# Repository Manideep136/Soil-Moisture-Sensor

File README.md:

# Soil Moisture Sensor PCB Using KiCad

## 📌 Project Overview

This project is a **Soil Moisture Sensor PCB** designed using KiCad 9. It detects the moisture level in soil using two conductive probes and an electronic sensing circuit.

The circuit uses an LM358 operational amplifier, a 10 kΩ potentiometer, resistors, capacitors, and indicator LEDs to detect changes in soil conductivity. The PCB includes two long sensing prongs that can be inserted into the soil.

The main objective of this project is to understand soil moisture detection, analog sensing circuits, and PCB design.

## 🎯 Objectives

- Design a soil moisture sensing circuit.
- Understand how soil conductivity changes with moisture.
- Use the LM358 for signal conditioning or threshold detection.
- Adjust the detection threshold using a potentiometer.
- Indicate the sensor status using LEDs.
- Design the schematic in KiCad.
- Assign component footprints.
- Create and route the PCB.
- Perform ERC and DRC checks.
- Visualize the completed PCB using KiCad's 3D Viewer.

## ⚙️ Working Principle

The sensor works by detecting changes in the electrical conductivity of soil.

The two sensing prongs act as electrodes. When inserted into soil, the electrical resistance between the electrodes changes depending on the soil's moisture content.

- **Wet soil:** Generally provides a lower resistance between the probes because it contains more conductive moisture.
- **Dry soil:** Generally provides a higher resistance between the probes.

The sensing circuit detects this change and provides a corresponding electrical signal.

The LM358 processes the sensing signal. The 10 kΩ potentiometer can be used to adjust the detection threshold, depending on the circuit configuration. The LEDs indicate the detected condition according to the actual circuit connections.

**Note:** The exact LED behavior depends on the schematic. Confirm which LED indicates wet or dry soil before using the sensor.

## 🔌 Block Diagram

```text
       Soil Moisture
             |
             v
      Two Sensing Probes
             |
             v
      Sensing Circuit
             |
             v
        LM358 Circuit
             |
             v
       Indicator LEDs
```

## 🧩 Components Used

| Reference | Component | Value / Type |
|---|---|---|
| U1 | Operational amplifier | LM358 |
| RV1 | Potentiometer | 10 kΩ |
| R1 | Resistor | 1 kΩ |
| R2 | Resistor | 10 kΩ |
| R3 | Resistor | 1 kΩ |
| D1 | Indicator LED | As selected |
| D2 | Indicator LED | As selected |
| C1 | Capacitor | As per schematic |
| C2 | Capacitor | As per schematic |
| J1, J2 | Connectors | As per schematic |
| Sensor probes | Conductive electrodes | PCB prongs |

*Verify the component values and reference designators against the final KiCad schematic before manufacturing.*

## 🖥️ PCB Design Using KiCad

The PCB was designed using KiCad 9.

### Design Process

1. Create the soil moisture sensor schematic.
2. Add the LM358, resistors, capacitors, potentiometer, LEDs, and connectors.
3. Connect the components according to the circuit diagram.
4. Assign suitable footprints.
5. Update the PCB from the schematic.
6. Arrange the components in the upper section of the board.
7. Design the fork-shaped sensing prongs.
8. Route the copper tracks.
9. Configure the board outline using the `Edge.Cuts` layer.
10. Run ERC in the schematic editor.
11. Run DRC in the PCB editor.
12. Inspect the completed board using the 3D Viewer.

## 📐 PCB Design Features

- Compact circuit layout.
- Two extended sensing prongs.
- LM358-based sensing circuit.
- Adjustable detection threshold.
- LED status indication.
- Dedicated component and connector placement.
- PCB layout designed in KiCad.

## 📁 Project Structure

```text
Soil-Moisture-Sensor/
├── Soil-Moisture-Sensor.kicad_pro
├── Soil-Moisture-Sensor.kicad_sch
├── Soil-Moisture-Sensor.kicad_pcb
├── README.md
└── Images/
    ├── schematic.png
    ├── pcb_layout.png
    └── 3d_view.png
```

## 🧪 Testing Procedure

1. Inspect the PCB for solder bridges and incorrect connections.
2. Verify the LM358 pinout and component orientation.
3. Check the potentiometer connections.
4. Verify LED polarity and resistor values.
5. Run ERC and DRC in KiCad.
6. Power the circuit using the specified supply voltage.
7. Insert the sensing prongs into soil with different moisture levels.
8. Adjust the potentiometer to set the detection threshold.
9. Observe the LED response.
10. Repeat the test with dry and moist soil.

## ⚠️ Design Considerations

- Use the correct supply voltage for the LM358 circuit.
- Ensure the two sensing electrodes remain electrically separate.
- Keep the sensing area free of solder mask if direct soil contact is required.
- Prevent the circuit section from contacting wet soil.
- Protect the electronics from water and corrosion.
- Use suitable PCB clearances and track widths.
- Avoid applying excessive voltage directly to the sensing probes.
- Verify the actual detection threshold experimentally.

## ✅ Advantages

- Simple and compact design.
- Adjustable moisture detection threshold.
- Visual status indication using LEDs.
- Easy to study and modify.
- Suitable for learning analog electronics and PCB design.
- Can be adapted for basic gardening and soil-monitoring experiments.

## 🚀 Future Improvements

- Add an Arduino or ESP32 interface.
- Display the moisture level on an LCD or OLED.
- Add an analog output connector.
- Implement digital soil moisture monitoring.
- Add wireless monitoring using Wi-Fi.
- Improve electrode corrosion resistance.
- Develop an automatic plant-watering system.

## 📚 Learning Outcomes

Through this project, I learned:

- Soil conductivity and moisture sensing.
- Basic analog sensing circuits.
- LM358 operational amplifier applications.
- Potentiometer-based threshold adjustment.
- LED indicator circuits.
- KiCad schematic design.
- Footprint assignment and PCB routing.
- PCB outline design.
- ERC and DRC verification.
- PCB 3D visualization.

## 🛠️ Software Used

**KiCad 9.0**

## 📄 License

This project is intended for educational and learning purposes. The circuit can be modified and improved for personal electronics projects.

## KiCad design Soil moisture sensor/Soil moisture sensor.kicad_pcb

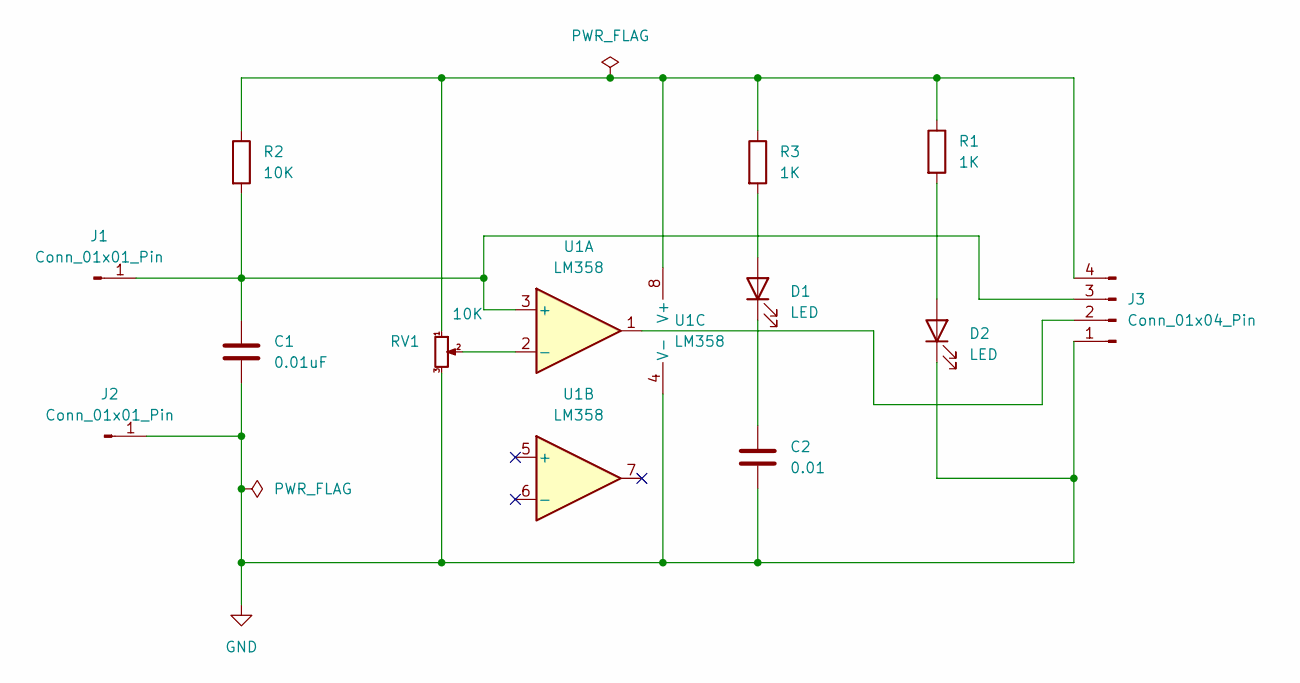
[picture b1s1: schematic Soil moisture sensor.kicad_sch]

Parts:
C1: 0.01uF; C_0805_2012Metric
C2: 0.01; C_0805_2012Metric
D1, D2: LED; LED_0805_2012Metric
J1, J2: Conn_01x01_Pin; SolderWire-0.1sqmm_1x01_D0.4mm_OD1mm
J3: Conn_01x04_Pin; PinHeader_1x04_P2.54mm_Vertical
R1, R3: 1K; R_0805_2012Metric
R2: 10K; R_0805_2012Metric
RV1: 10K; Potentiometer_ACP_CA9-H2,5_Horizontal
U1: LM358; DIP-8_W7.62mm

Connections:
GND: C1.2, C2.2, D2.1 (K), J2.1 (Pin_1_1), J3.1, RV1.3, U1.4 (V-)
unnamed: D1.2 (A), R3.2
unnamed: C2.1, D1.1 (K)
unnamed: D2.2 (A), R1.2
unnamed: C1.1, J1.1 (Pin_1_1), J3.3, R2.2, U1.3 (+)
unnamed: J3.2, U1.1
unnamed: J3.4, R1.1, R2.1, R3.1, RV1.1, U1.8 (V+)
unnamed: RV1.2, U1.2 (-)

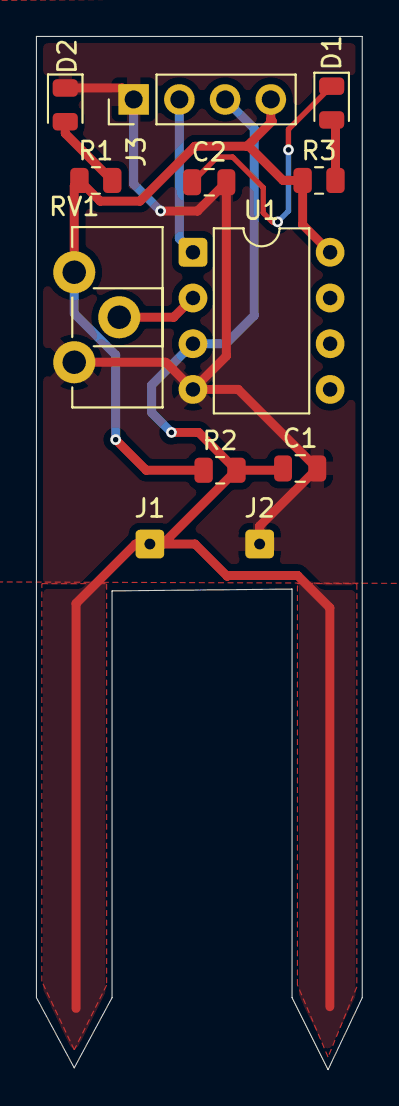
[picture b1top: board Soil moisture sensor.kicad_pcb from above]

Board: 2 copper layers, 18.1 x 57.4 mm, 12 parts (0 on the bottom side), 8 nets.
